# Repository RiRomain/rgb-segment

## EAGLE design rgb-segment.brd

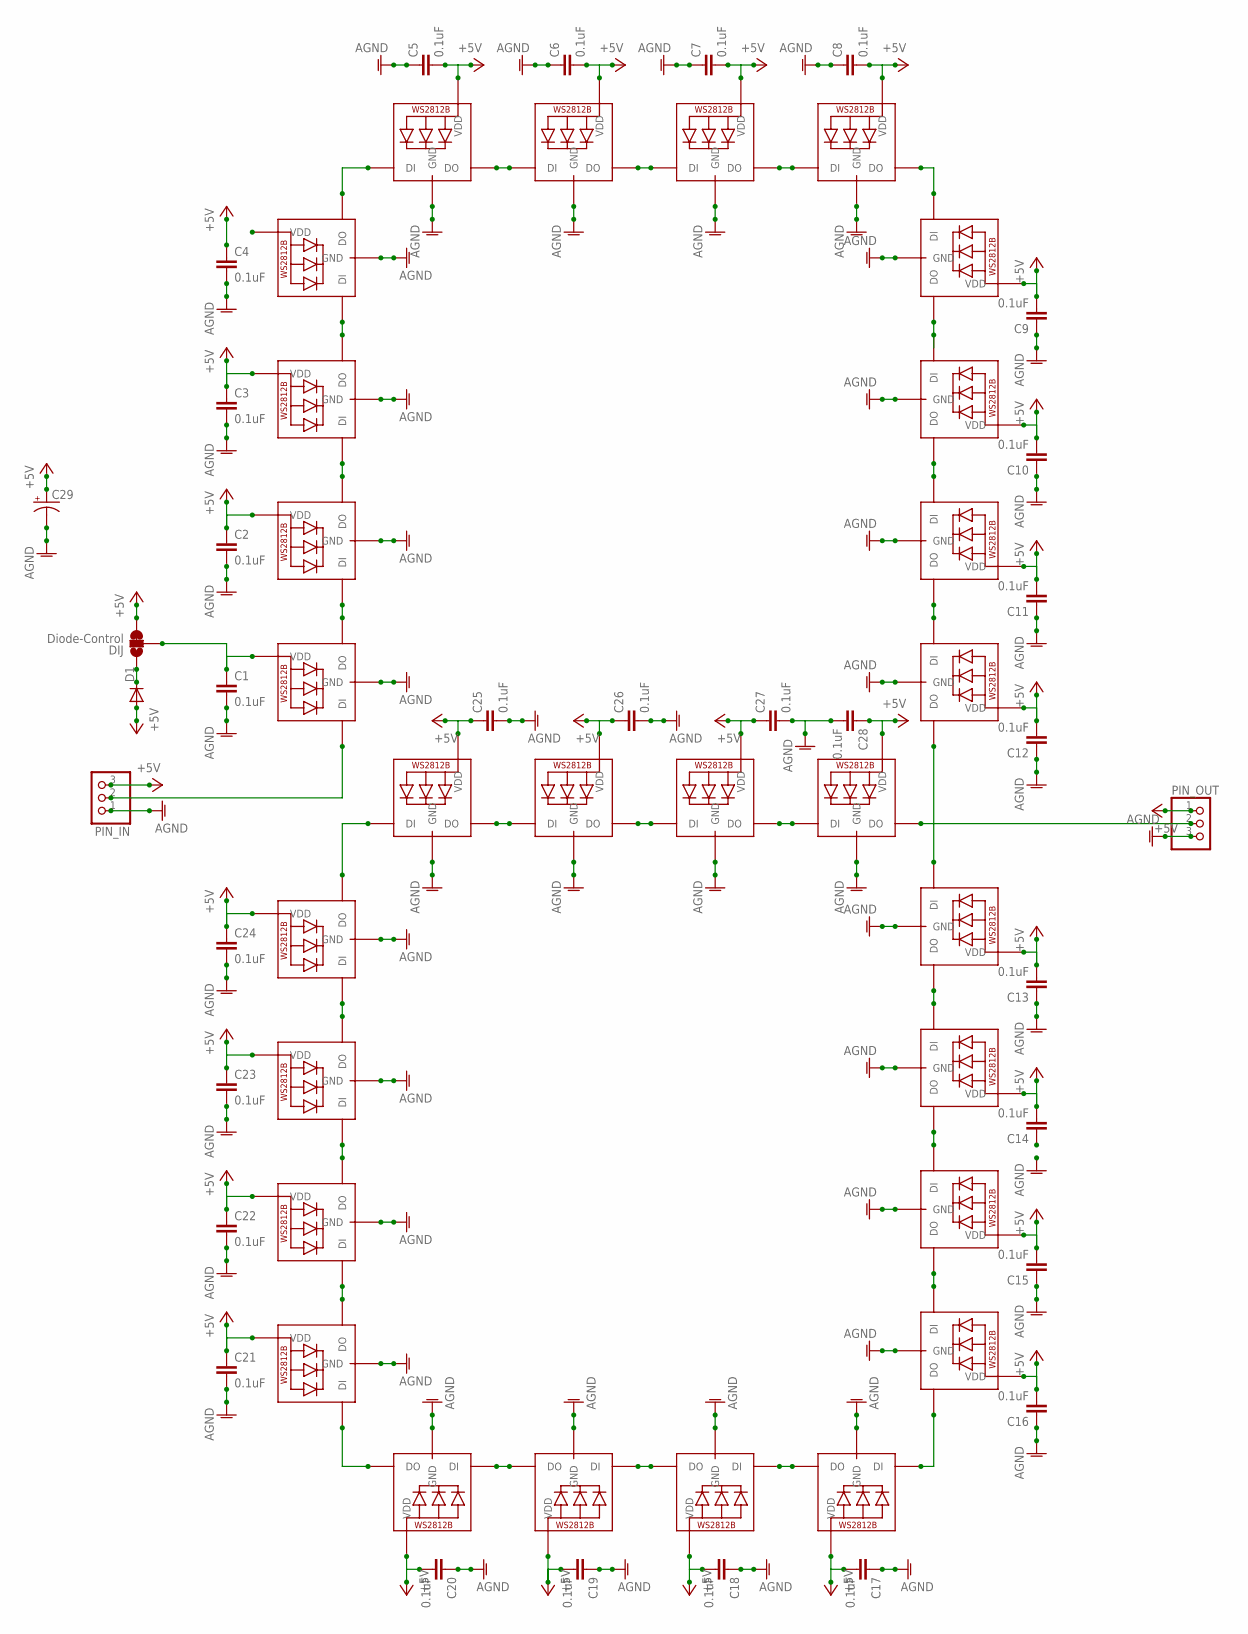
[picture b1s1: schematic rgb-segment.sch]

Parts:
C1, C2, C3, C4, C5, C6, C7, C8, C9, C10, C11, C12, C13, C14, C15, C16, C17, C18, C19, C20, C21, C22, C23, C24, C25, C26, C27, C28: 0.1uF; C0805
C29: CAP_POLG; PANASONIC_G
D1: DIODE-DO214AC; DO214AC
DIJ: Diode-Control; PAD-JUMPER-3-2OF3_NC_BY_TRACE_YES_SILK_FULL_BOX
LED1, LED2, LED3, LED4, LED5, LED6, LED7, LED8, LED9, LED10, LED11, LED12, LED13, LED14, LED15, LED16, LED17, LED18, LED19, LED20, LED21, LED22, LED23, LED24, LED25, LED26, LED27, LED28: WS2812B_5050N; WS2812B-NARROW
PIN_IN: PINHD-1X3; 1X03
PIN_OUT: PINHD-1X3; 1X03

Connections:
+5V: C2.1, C3.1, C4.1, C5.2, C6.2, C7.2, C8.2, C9.2, C10.2, C11.2, C12.2, C13.2, C14.2, C15.2, C16.2, C17.2, C18.2, C19.2, C20.2, C21.1, C22.1, C23.1, C24.1, C25.1, C26.1, C27.1, C28.1, C29.+, D1.A, DIJ.3, LED2.1-VDD (VDD), LED3.1-VDD (VDD), LED5.1-VDD (VDD), LED6.1-VDD (VDD), LED7.1-VDD (VDD), LED8.1-VDD (VDD), LED9.1-VDD (VDD), LED10.1-VDD (VDD), LED11.1-VDD (VDD), LED12.1-VDD (VDD), LED13.1-VDD (VDD), LED14.1-VDD (VDD), LED15.1-VDD (VDD), LED16.1-VDD (VDD), LED17.1-VDD (VDD), LED18.1-VDD (VDD), LED19.1-VDD (VDD), LED20.1-VDD (VDD), LED21.1-VDD (VDD), LED22.1-VDD (VDD), LED23.1-VDD (VDD), LED24.1-VDD (VDD), LED25.1-VDD (VDD), LED26.1-VDD (VDD), LED27.1-VDD (VDD), LED28.1-VDD (VDD), PIN_IN.3, PIN_OUT.1
AGND: C1.2, C2.2, C3.2, C4.2, C5.1, C6.1, C7.1, C8.1, C9.1, C10.1, C11.1, C12.1, C13.1, C15.1, C16.1, C17.1, C18.1, C19.1, C20.1, C21.2, C22.2, C23.2, C24.2, C25.2, C26.2, C27.2, C28.2, C29.-, LED1.3-GND (GND), LED2.3-GND (GND), LED3.3-GND (GND), LED4.3-GND (GND), LED5.3-GND (GND), LED6.3-GND (GND), LED7.3-GND (GND), LED8.3-GND (GND), LED9.3-GND (GND), LED10.3-GND (GND), LED11.3-GND (GND), LED12.3-GND (GND), LED13.3-GND (GND), LED14.3-GND (GND), LED15.3-GND (GND), LED16.3-GND (GND), LED17.3-GND (GND), LED18.3-GND (GND), LED19.3-GND (GND), LED20.3-GND (GND), LED21.3-GND (GND), LED22.3-GND (GND), LED23.3-GND (GND), LED24.3-GND (GND), LED25.3-GND (GND), LED26.3-GND (GND), LED27.3-GND (GND), LED28.3-GND (GND), PIN_IN.1, PIN_OUT.3
unnamed: LED17.2-DOUT (DO), LED18.4-DIN (DI)
unnamed: LED18.2-DOUT (DO), LED19.4-DIN (DI)
unnamed: LED1.4-DIN (DI), PIN_IN.2
unnamed: LED19.2-DOUT (DO), LED20.4-DIN (DI)
unnamed: C1.1, DIJ.2, LED1.1-VDD (VDD)
unnamed: D1.C, DIJ.1
unnamed: LED5.2-DOUT (DO), LED6.4-DIN (DI)
unnamed: LED6.2-DOUT (DO), LED7.4-DIN (DI)
unnamed: LED7.2-DOUT (DO), LED8.4-DIN (DI)
unnamed: LED8.2-DOUT (DO), LED9.4-DIN (DI)
unnamed: LED28.2-DOUT (DO), PIN_OUT.2
unnamed: LED4.2-DOUT (DO), LED5.4-DIN (DI)
unnamed: LED3.2-DOUT (DO), LED4.4-DIN (DI)
unnamed: LED9.2-DOUT (DO), LED10.4-DIN (DI)
unnamed: LED10.2-DOUT (DO), LED11.4-DIN (DI)
unnamed: LED2.2-DOUT (DO), LED3.4-DIN (DI)
unnamed: LED1.2-DOUT (DO), LED2.4-DIN (DI)
unnamed: LED11.2-DOUT (DO), LED12.4-DIN (DI)
unnamed: LED12.2-DOUT (DO), LED13.4-DIN (DI)
unnamed: LED24.2-DOUT (DO), LED25.4-DIN (DI)
unnamed: LED13.2-DOUT (DO), LED14.4-DIN (DI)
unnamed: LED14.2-DOUT (DO), LED15.4-DIN (DI)
unnamed: LED15.2-DOUT (DO), LED16.4-DIN (DI)
unnamed: LED16.2-DOUT (DO), LED17.4-DIN (DI)
unnamed: LED20.2-DOUT (DO), LED21.4-DIN (DI)
unnamed: LED21.2-DOUT (DO), LED22.4-DIN (DI)
unnamed: LED22.2-DOUT (DO), LED23.4-DIN (DI)
unnamed: LED23.2-DOUT (DO), LED24.4-DIN (DI)
unnamed: LED25.2-DOUT (DO), LED26.4-DIN (DI)
unnamed: LED26.2-DOUT (DO), LED27.4-DIN (DI)
unnamed: LED27.2-DOUT (DO), LED28.4-DIN (DI)

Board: 2 copper layers, 61 parts (0 on the bottom side), 33 nets, no tracks yet.

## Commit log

2016-07-14 :confetti_ball: Added .gitattributes
2016-07-18 Completition of the schema - First version of the board - 17-07-2016

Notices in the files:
parts and their libraries:
SparkFun-Passives: Licensing: Creative Commons ShareAlike 4.0 International - https://creativecommons.org/licenses/by-sa/4.0
